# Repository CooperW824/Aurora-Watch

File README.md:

# Aurora-Watch
Project Aurora: The most over-engineered gimmick ever. A watch that is a compass, thermometer, step-counter, flashlight, all with a rechargable battery, and a processor 50x faster than the Apollo Guidance Computer.

## What is it?

It is a custom designed printed circuit board that contains a ring of 12 RGB LEDs, a microcontroller, and some senors to:
1. Display the current time. Where the red LED represents the hour hand, the green LED is the minute hand and the blue LED is the second hand.
2. Display the current ambient temperature using the number of LEDs lit and the color of the LEDs for the temperature.
3. A magnetic compass with the red LED pointing north, and the blue LED pointing south
4. A read out of the current battery charge using the LEDs
5. A built in step counter
5. A flashlight that uses the red LEDs to create a red-light flashlight
6. Rechargable LiPO battery using USB-C

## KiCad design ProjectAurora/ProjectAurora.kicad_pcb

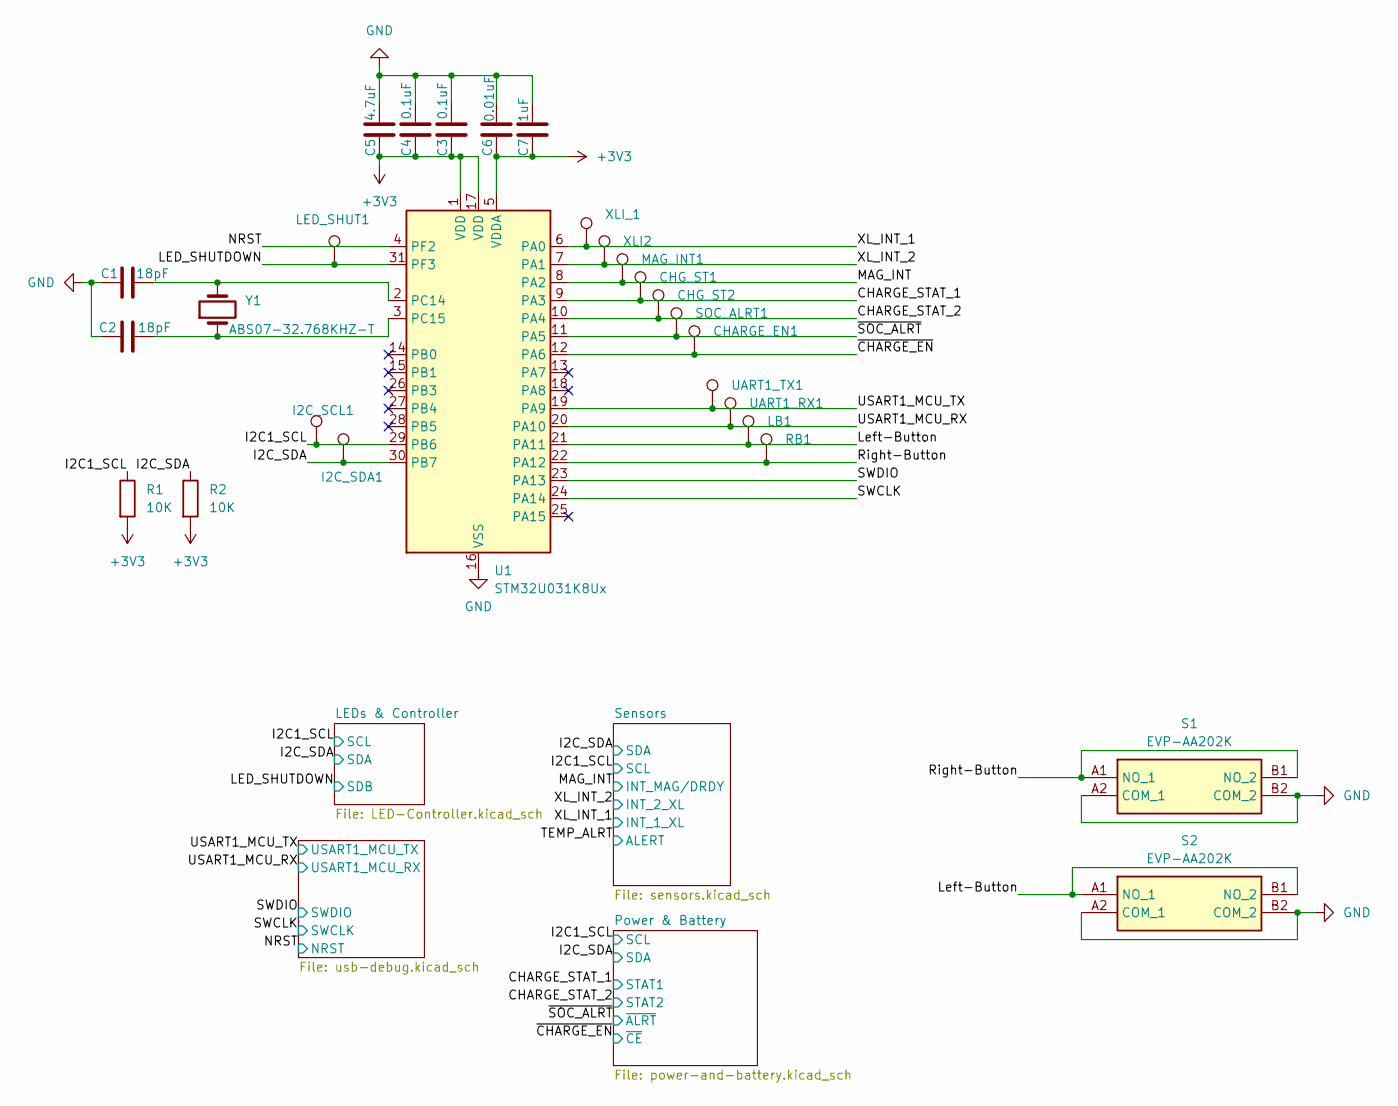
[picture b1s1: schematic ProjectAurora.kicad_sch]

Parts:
C1, C2: 18pF; C_0603_1608Metric
C3, C4: 0.1uF; C_0603_1608Metric
C5: 4.7uF; C_0603_1608Metric
C6: 0.01uF; C_0603_1608Metric
C7: 1uF; C_0603_1608Metric
CHARGE_EN1: TestPoint; TestPoint_Pad_1.0x1.0mm
CHG_ST1, CHG_ST2: TestPoint; TestPoint_Pad_1.0x1.0mm
I2C_SCL1, I2C_SDA1: TestPoint; TestPoint_Pad_1.0x1.0mm
LB1: TestPoint; TestPoint_Pad_1.0x1.0mm
LED_SHUT1: TestPoint; TestPoint_Pad_1.0x1.0mm
MAG_INT1: TestPoint; TestPoint_Pad_1.0x1.0mm
R1, R2: 10K; R_0603_1608Metric
RB1: TestPoint; TestPoint_Pad_1.0x1.0mm
S1, S2: EVP-AA202K; EVPAA202K; Mouser Part Number 667-EVP-AA202K
SOC_ALRT1: TestPoint; TestPoint_Pad_1.0x1.0mm
U1: STM32U031K8Ux; QFN-32-1EP_5x5mm_P0.5mm_EP3.45x3.45mm
UART1_RX1, UART1_TX1: TestPoint; TestPoint_Pad_1.0x1.0mm
XLI2: TestPoint; TestPoint_Pad_1.0x1.0mm
XLI_1: TestPoint; TestPoint_Pad_1.0x1.0mm
Y1: ABS07-32.768KHZ-T; ABS07

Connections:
/CHARGE_STAT_1: CHG_ST1.1, U1.9 (PA3); also elsewhere on the board
/CHARGE_STAT_2: CHG_ST2.1, U1.10 (PA4); also elsewhere on the board
/I2C1_SCL: I2C_SCL1.1, R1.1, U1.29 (PB6); also elsewhere on the board
/I2C_SDA: I2C_SDA1.1, R2.1, U1.30 (PB7); also elsewhere on the board
/LED_SHUTDOWN: LED_SHUT1.1, U1.31 (PF3); also elsewhere on the board
/Left-Button: LB1.1, S2.A1 (NO_1), S2.B1 (NO_2), U1.21 (PA11)
/MAG_INT: MAG_INT1.1, U1.8 (PA2); also elsewhere on the board
/NRST: U1.4 (PF2); also elsewhere on the board
/Right-Button: RB1.1, S1.A1 (NO_1), S1.B1 (NO_2), U1.22 (PA12)
/SWCLK: U1.24 (PA14); also elsewhere on the board
/SWDIO: U1.23 (PA13); also elsewhere on the board
/USART1_MCU_RX: U1.20 (PA10), UART1_RX1.1; also elsewhere on the board
/USART1_MCU_TX: U1.19 (PA9), UART1_TX1.1; also elsewhere on the board
/XL_INT_1: U1.6 (PA0), XLI_1.1; also elsewhere on the board
/XL_INT_2: U1.7 (PA1), XLI2.1; also elsewhere on the board
/~CHARGE_EN: CHARGE_EN1.1, U1.12 (PA6); also elsewhere on the board
/~SOC_ALRT: SOC_ALRT1.1, U1.11 (PA5); also elsewhere on the board
GND: C1.1, C2.1, C3.2, C4.2, C5.2, C6.2, C7.2, S1.A2 (COM_1), S1.B2 (COM_2), S2.A2 (COM_1), S2.B2 (COM_2), U1.16 (VSS), U1.32 (VSS), U1.33 (VSS); also elsewhere on the board
unnamed: C1.2, U1.2 (PC14), Y1.2
unnamed: C2.2, U1.3 (PC15), Y1.1

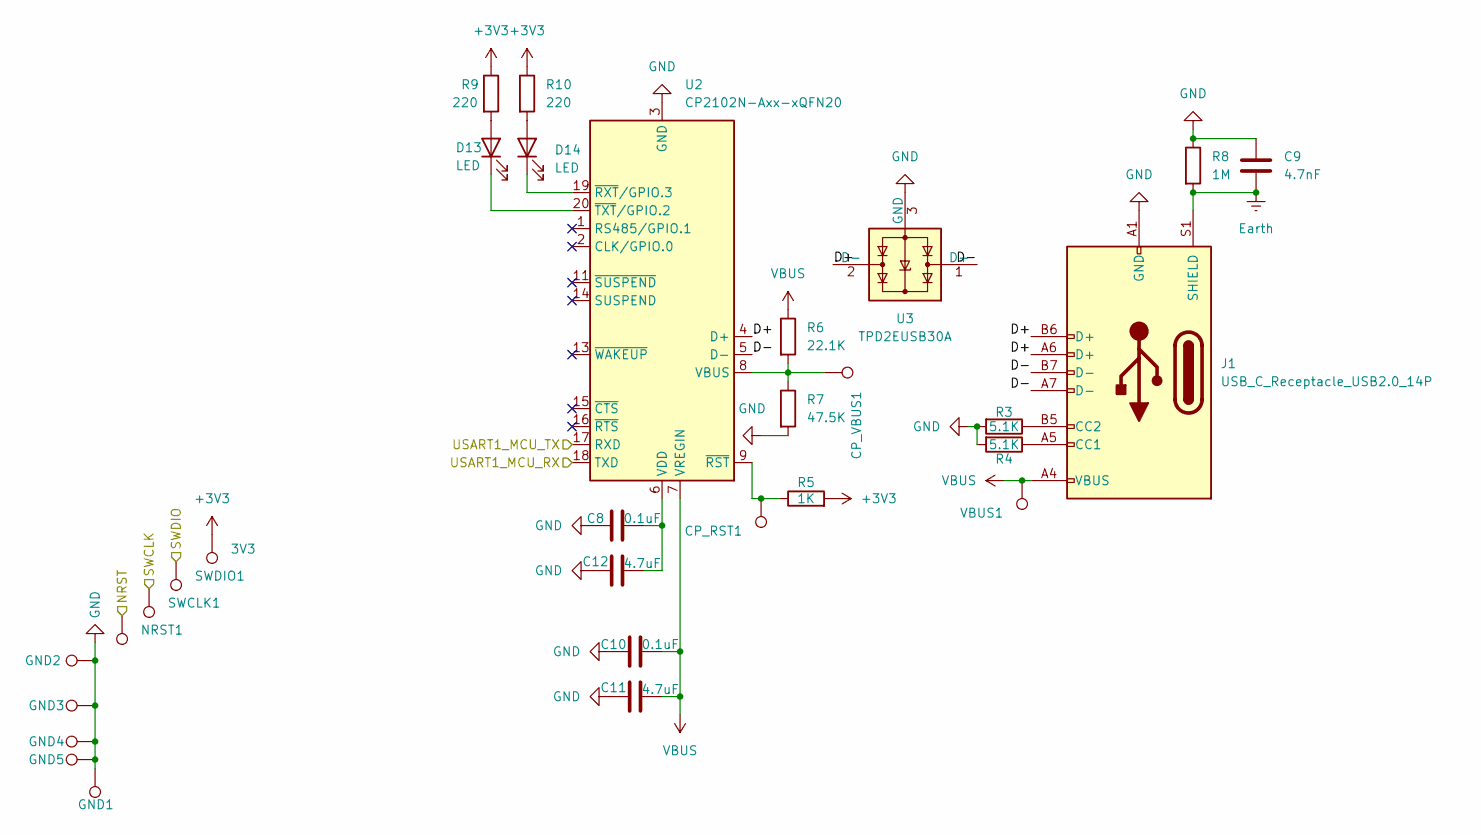
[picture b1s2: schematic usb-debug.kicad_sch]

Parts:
3V3: TestPoint; TestPoint_Pad_2.0x2.0mm
C8, C10: 0.1uF; C_0603_1608Metric
C9: 4.7nF; C_0603_1608Metric
C11, C12: 4.7uF; C_0603_1608Metric
CP_RST1: TestPoint; TestPoint_Pad_1.0x1.0mm
CP_VBUS1: TestPoint; TestPoint_Pad_1.0x1.0mm
D13, D14: LED; LED_0603_1608Metric
GND1: TestPoint; TestPoint_Pad_2.0x2.0mm
GND2, GND3, GND4, GND5: TestPoint; TestPoint_Pad_1.0x1.0mm
J1: USB_C_Receptacle_USB2.0_14P; USB_C_Receptacle_GCT_USB4105-xx-A_16P_TopMnt_Horizontal
NRST1: TestPoint; TestPoint_Pad_1.0x1.0mm
R3, R4: 5.1K; R_0603_1608Metric
R5: 1K; R_0603_1608Metric
R6: 22.1K; R_0603_1608Metric
R7: 47.5K; R_0603_1608Metric
R8: 1M; R_0603_1608Metric
R9, R10: 220; R_0603_1608Metric
SWCLK1: TestPoint; TestPoint_Pad_2.0x2.0mm
SWDIO1: TestPoint; TestPoint_Pad_2.0x2.0mm
U2: CP2102N-Axx-xQFN20; SiliconLabs_QFN-20-1EP_3x3mm_P0.5mm_EP1.8x1.8mm
U3: TPD2EUSB30A; Texas_DRT-3
VBUS1: TestPoint; TestPoint_Pad_1.0x1.0mm

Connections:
/NRST: NRST1.1; also elsewhere on the board
/SWCLK: SWCLK1.1; also elsewhere on the board
/SWDIO: SWDIO1.1; also elsewhere on the board
/USART1_MCU_RX: U2.18 (TXD); also elsewhere on the board
/USART1_MCU_TX: U2.17 (RXD); also elsewhere on the board
/USB & Debug/D+: J1.A6 (D+), J1.B6 (D+), U2.4 (D+), U3.2 (D-)
/USB & Debug/D-: J1.A7 (D-), J1.B7 (D-), U2.5 (D-), U3.1 (D+)
Earth: C9.2, J1.S1 (SHIELD), R8.2
GND: C8.1, C9.1, C10.1, C11.1, C12.1, GND1.1, GND2.1, GND3.1, GND4.1, GND5.1, J1.A1 (GND), J1.A12 (GND), J1.B1 (GND), J1.B12 (GND), R3.2, R4.2, R7.2, R8.1, U2.3 (GND), U2.12 (GND), U2.21 (GND), U3.3 (GND); also elsewhere on the board
unnamed: D13.2 (A), R9.2
unnamed: D13.1 (K), U2.20 (~TXT/GPIO.2)
unnamed: D14.2 (A), R10.2
unnamed: D14.1 (K), U2.19 (~RXT/GPIO.3)
unnamed: J1.A5 (CC1), R4.1
unnamed: J1.B5 (CC2), R3.1
unnamed: CP_VBUS1.1, R6.2, R7.1, U2.8 (VBUS)
unnamed: C8.2, C12.2, U2.6 (VDD)
unnamed: CP_RST1.1, R5.1, U2.9 (~RST)
VBUS: C10.2, C11.2, J1.A4 (VBUS), J1.A9 (VBUS), J1.B4 (VBUS), J1.B9 (VBUS), R6.1, U2.7 (VREGIN), VBUS1.1; also elsewhere on the board

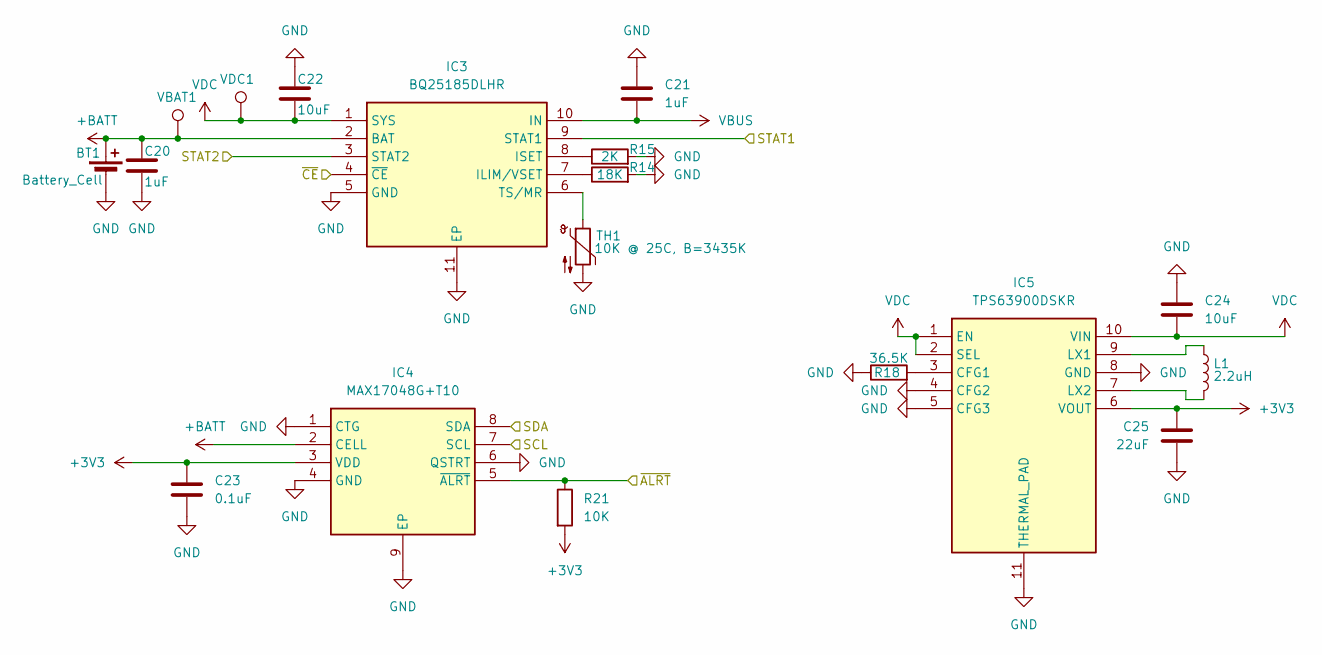
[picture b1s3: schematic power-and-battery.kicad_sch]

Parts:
BT1: Battery_Cell; JST_SH_SM02B-SRSS-TB_1x02-1MP_P1.00mm_Horizontal
C20, C21: 1uF; C_0603_1608Metric
C22, C24: 10uF; C_0603_1608Metric
C23: 0.1uF; C_0603_1608Metric
C25: 22uF; C_0603_1608Metric
IC3: BQ25185DLHR; Texas_DLH0010A_WSON-10-1EP_2.2x2mm_P0.4mm_EP0.9x1.5mm_Therm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; Mouser Part Number 595-BQ25185DLHR
IC4: MAX17048G+T10; TDFN-8-1EP_2x2mm_P0.5mm_EP0.8x1.2mm; Mouser Part Number 700-MAX17048G+T10
IC5: TPS63900DSKR; WSON-10-1EP_2.5x2.5mm_P0.5mm_EP1.2x2mm; Mouser Part Number 595-TPS63900DSKR
L1: 2.2uH; L_Coilcraft_0805HQ_2012Metric
R14: 18K; R_0603_1608Metric
R15: 2K; R_0603_1608Metric
R18: 36.5K; R_0603_1608Metric
R21: 10K; R_0603_1608Metric
TH1: 10K @ 25C, B=3435K; R_0603_1608Metric
VBAT1: TestPoint; TestPoint_Pad_1.0x1.0mm
VDC1: TestPoint; TestPoint_Pad_1.0x1.0mm

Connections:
+BATT: BT1.1 (+), C20.1, IC3.2 (BAT), IC4.2 (CELL), VBAT1.1
/CHARGE_STAT_1: IC3.9 (STAT1); also elsewhere on the board
/CHARGE_STAT_2: IC3.3 (STAT2); also elsewhere on the board
/I2C1_SCL: IC4.7 (SCL); also elsewhere on the board
/I2C_SDA: IC4.8 (SDA); also elsewhere on the board
/~CHARGE_EN: IC3.4 (~CE); also elsewhere on the board
/~SOC_ALRT: IC4.5 (~ALRT), R21.1; also elsewhere on the board
GND: BT1.2 (-), C20.2, C21.1, C22.1, C23.2, C24.1, C25.1, IC3.5 (GND), IC3.11 (EP), IC4.1 (CTG), IC4.4 (GND), IC4.6 (QSTRT), IC4.9 (EP), IC5.4 (CFG2), IC5.5 (CFG3), IC5.8 (GND), IC5.11 (THERMAL_PAD), R14.2, R15.2, R18.1, TH1.2; also elsewhere on the board
unnamed: IC3.7 (ILIM/VSET), R14.1
unnamed: IC3.8 (ISET), R15.1
unnamed: IC3.6 (TS/MR), TH1.1
unnamed: IC5.3 (CFG1), R18.2
unnamed: IC5.9 (LX1), L1.1
unnamed: IC5.7 (LX2), L1.2
VBUS: C21.2, IC3.10 (IN); also elsewhere on the board
VDC: C22.2, C24.2, IC3.1 (SYS), IC5.1 (EN), IC5.2 (SEL), IC5.10 (VIN), VDC1.1

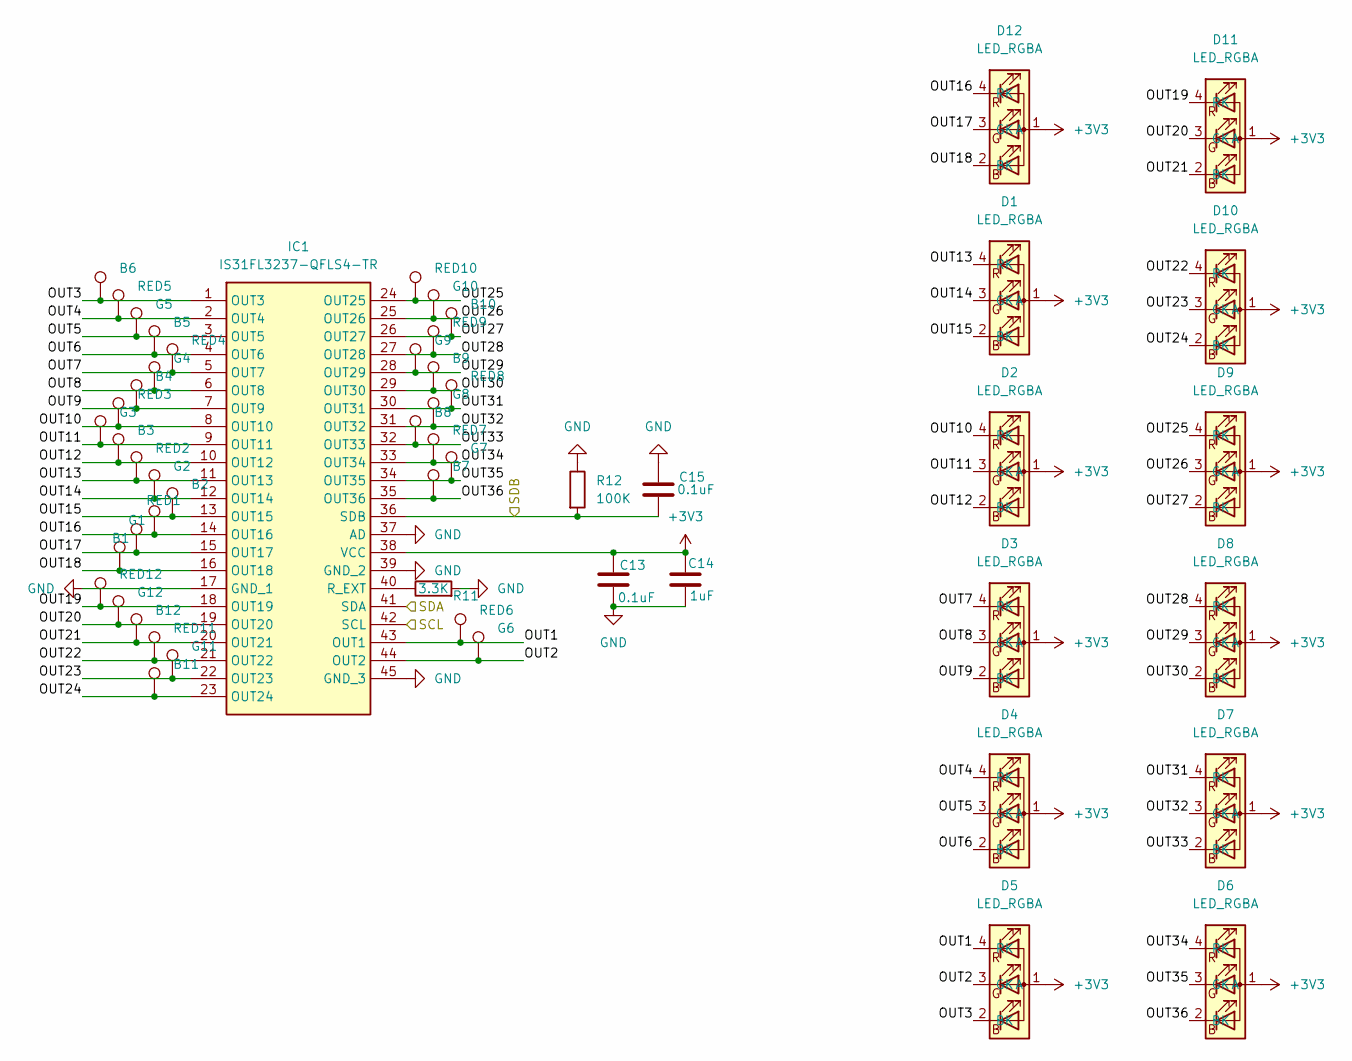
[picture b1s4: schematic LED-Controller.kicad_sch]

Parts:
B1, B2, B3, B4, B5, B6, B8, B9, B10, B11, B12: TestPoint; TestPoint_Pad_1.0x1.0mm
B7: `; TestPoint_Pad_1.0x1.0mm
C13, C15: 0.1uF; C_0603_1608Metric
C14: 1uF; C_0603_1608Metric
D1, D2, D3, D4, D5, D6, D7, D8, D9, D10, D11, D12: LED_RGBA; XL-1615RGBC-YG
G1, G2, G3, G4, G5, G6, G7, G8, G9, G10, G11, G12: TestPoint; TestPoint_Pad_1.0x1.0mm
IC1: IS31FL3237-QFLS4-TR; IS31FL3237QFLS4TR; Mouser Part Number 870-IS31FL3237QFLS4T
R11: 3.3K; R_0603_1608Metric
R12: 100K; R_0603_1608Metric
RED1, RED2, RED3, RED4, RED5, RED6, RED7, RED8, RED9, RED10, RED11, RED12: TestPoint; TestPoint_Pad_1.0x1.0mm

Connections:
/I2C1_SCL: IC1.42 (SCL); also elsewhere on the board
/I2C_SDA: IC1.41 (SDA); also elsewhere on the board
/LED_SHUTDOWN: C15.2, IC1.36 (SDB), R12.2; also elsewhere on the board
/LEDs & Controller/OUT1: D5.4 (RK), IC1.43 (OUT1), RED6.1
/LEDs & Controller/OUT2: D5.3 (GK), G6.1, IC1.44 (OUT2)
/LEDs & Controller/OUT3: B6.1, D5.2 (BK), IC1.1 (OUT3)
/LEDs & Controller/OUT4: D4.4 (RK), IC1.2 (OUT4), RED5.1
/LEDs & Controller/OUT5: D4.3 (GK), G5.1, IC1.3 (OUT5)
/LEDs & Controller/OUT6: B5.1, D4.2 (BK), IC1.4 (OUT6)
/LEDs & Controller/OUT7: D3.4 (RK), IC1.5 (OUT7), RED4.1
/LEDs & Controller/OUT8: D3.3 (GK), G4.1, IC1.6 (OUT8)
/LEDs & Controller/OUT9: B4.1, D3.2 (BK), IC1.7 (OUT9)
/LEDs & Controller/OUT10: D2.4 (RK), IC1.8 (OUT10), RED3.1
/LEDs & Controller/OUT11: D2.3 (GK), G3.1, IC1.9 (OUT11)
/LEDs & Controller/OUT12: B3.1, D2.2 (BK), IC1.10 (OUT12)
/LEDs & Controller/OUT13: D1.4 (RK), IC1.11 (OUT13), RED2.1
/LEDs & Controller/OUT14: D1.3 (GK), G2.1, IC1.12 (OUT14)
/LEDs & Controller/OUT15: B2.1, D1.2 (BK), IC1.13 (OUT15)
/LEDs & Controller/OUT16: D12.4 (RK), IC1.14 (OUT16), RED1.1
/LEDs & Controller/OUT17: D12.3 (GK), G1.1, IC1.15 (OUT17)
/LEDs & Controller/OUT18: B1.1, D12.2 (BK), IC1.16 (OUT18)
/LEDs & Controller/OUT19: D11.4 (RK), IC1.18 (OUT19), RED12.1
/LEDs & Controller/OUT20: D11.3 (GK), G12.1, IC1.19 (OUT20)
/LEDs & Controller/OUT21: B12.1, D11.2 (BK), IC1.20 (OUT21)
/LEDs & Controller/OUT22: D10.4 (RK), IC1.21 (OUT22), RED11.1
/LEDs & Controller/OUT23: D10.3 (GK), G11.1, IC1.22 (OUT23)
/LEDs & Controller/OUT24: B11.1, D10.2 (BK), IC1.23 (OUT24)
/LEDs & Controller/OUT25: D9.4 (RK), IC1.24 (OUT25), RED10.1
/LEDs & Controller/OUT26: D9.3 (GK), G10.1, IC1.25 (OUT26)
/LEDs & Controller/OUT27: B10.1, D9.2 (BK), IC1.26 (OUT27)
/LEDs & Controller/OUT28: D8.4 (RK), IC1.27 (OUT28), RED9.1
/LEDs & Controller/OUT29: D8.3 (GK), G9.1, IC1.28 (OUT29)
/LEDs & Controller/OUT30: B9.1, D8.2 (BK), IC1.29 (OUT30)
/LEDs & Controller/OUT31: D7.4 (RK), IC1.30 (OUT31), RED8.1
/LEDs & Controller/OUT32: D7.3 (GK), G8.1, IC1.31 (OUT32)
/LEDs & Controller/OUT33: B8.1, D7.2 (BK), IC1.32 (OUT33)
/LEDs & Controller/OUT34: D6.4 (RK), IC1.33 (OUT34), RED7.1
/LEDs & Controller/OUT35: D6.3 (GK), G7.1, IC1.34 (OUT35)
/LEDs & Controller/OUT36: B7.1, D6.2 (BK), IC1.35 (OUT36)
GND: C13.2, C14.2, C15.1, IC1.17 (GND_1), IC1.37 (AD), IC1.39 (GND_2), IC1.45 (GND_3), R11.2, R12.1; also elsewhere on the board
unnamed: IC1.40 (R_EXT), R11.1

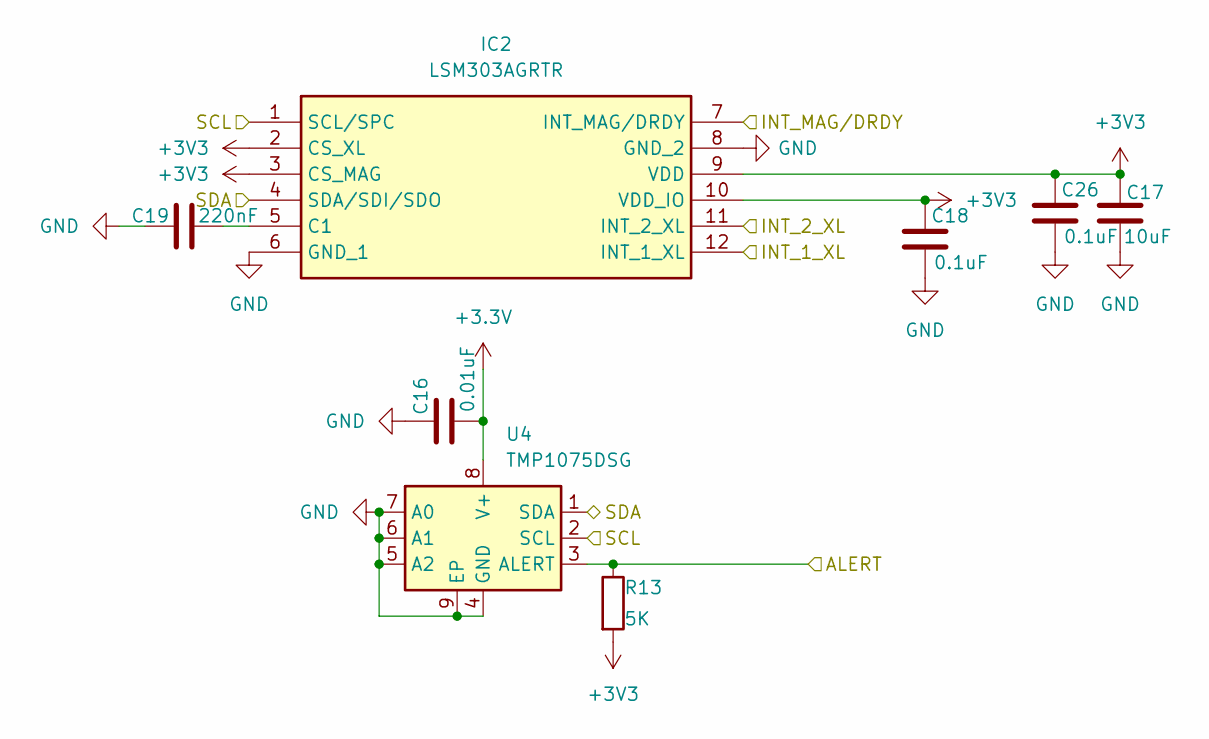
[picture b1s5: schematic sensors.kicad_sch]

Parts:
C16: 0.01uF; C_0603_1608Metric
C17: 10uF; C_0603_1608Metric
C18, C26: 0.1uF; C_0603_1608Metric
C19: 220nF; C_0603_1608Metric
IC2: LSM303AGRTR; LGA-12_2x2mm_P0.5mm; Mouser Part Number 511-LSM303AGRTR
R13: 5K; R_0603_1608Metric
U4: TMP1075DSG; WSON-8-1EP_2x2mm_P0.5mm_EP0.9x1.6mm_ThermalVias

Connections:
/I2C1_SCL: IC2.1 (SCL/SPC), U4.2 (SCL); also elsewhere on the board
/I2C_SDA: IC2.4 (SDA/SDI/SDO), U4.1 (SDA); also elsewhere on the board
/MAG_INT: IC2.7 (INT_MAG/DRDY); also elsewhere on the board
/XL_INT_1: IC2.12 (INT_1_XL); also elsewhere on the board
/XL_INT_2: IC2.11 (INT_2_XL); also elsewhere on the board
GND: C16.1, C17.2, C18.2, C19.2, C26.2, IC2.6 (GND_1), IC2.8 (GND_2), U4.4 (GND), U4.5 (A2), U4.6 (A1), U4.7 (A0), U4.9 (EP); also elsewhere on the board
unnamed: C19.1, IC2.5 (C1)
unnamed: R13.1, U4.3 (ALERT)

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
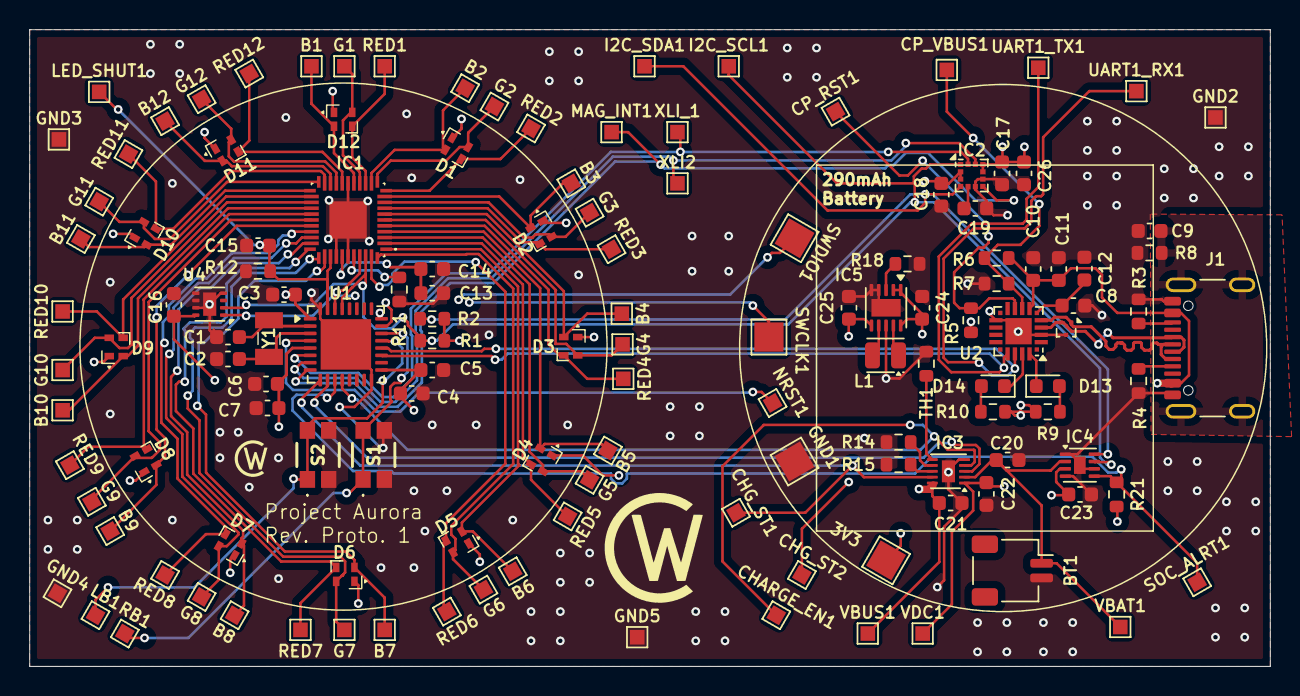
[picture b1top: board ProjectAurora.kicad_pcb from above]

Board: 4 copper layers, 84.8 x 43.5 mm, 136 parts (0 on the bottom side), 80 nets.

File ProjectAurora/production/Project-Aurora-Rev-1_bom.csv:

Designator,Footprint,Quantity,Value,LCSC Part #
"3V3, GND1, SWCLK1, SWDIO1",TestPoint_Pad_2.0x2.0mm,4,TestPoint,
"B1, B10, B11, B12, B2, B3, B4, B5, B6, B8, B9, CHARGE_EN1, CHG_ST1, CHG_ST2, CP_RST1, CP_VBUS1, G1, G10, G11, G12, G2, G3, G4, G5, G6, G7, G8, G9, GND2, GND3, GND4, GND5, I2C_SCL1, I2C_SDA1, LB1, LED_SHUT1, MAG_INT1, NRST1, RB1, RED1, RED10, RED11, RED12, RED2, RED3, RED4, RED5, RED6, RED7, RED8, RED9, SOC_ALRT1, UART1_RX1, UART1_TX1, VBAT1, VBUS1, VDC1, XLI2, XLI_1",TestPoint_Pad_1.0x1.0mm,59,TestPoint,
B7,TestPoint_Pad_1.0x1.0mm,1,`,
BT1,JST_SH_SM02B-SRSS-TB_1x02-1MP_P1.00mm_Horizontal,1,Battery_Cell,
"C1, C2",0603,2,18pF,
"C10, C13, C15, C18, C23, C26, C3, C4, C8",0603,9,0.1uF,
"C11, C12, C5",0603,3,4.7uF,
"C14, C20, C21, C7",0603,4,1uF,
"C16, C6",0603,2,0.01uF,
"C17, C22, C24",0603,3,10uF,
C19,0603,1,220nF,
C25,0603,1,22uF,
C9,0603,1,4.7nF,
"D1, D10, D11, D12, D2, D3, D4, D5, D6, D7, D8, D9",XL-1615RGBC-YG,12,LED_RGBA,
"D13, D14",0603,2,LED,
IC1,IS31FL3237QFLS4TR,1,IS31FL3237-QFLS4-TR,
IC2,LGA-12_2x2mm_P0.5mm,1,LSM303AGRTR,
IC3,Texas_DLH0010A_WSON-10-1EP_2.2x2mm_P0.4mm_EP0.9x1.5mm_ThermalVias,1,BQ25185DLHR,
IC4,TDFN-8-1EP_2x2mm_P0.5mm_EP0.8x1.2mm,1,MAX17048G+T10,
IC5,WSON-10-1EP_2.5x2.5mm_P0.5mm_EP1.2x2mm,1,TPS63900DSKR,
J1,USB_C_Receptacle_GCT_USB4105-xx-A_16P_TopMnt_Horizontal,1,USB_C_Receptacle_USB2.0_14P,
L1,L_Coilcraft_0805HQ_2012Metric,1,2.2uH,
"R1, R2, R21",0603,3,10K,
"R10, R9",0603,2,220,
R11,0603,1,3.3K,
R12,0603,1,100K,
R14,0603,1,18K,
R15,0603,1,2K,
R18,0603,1,36.5K,
"R3, R4",0603,2,5.1K,
R5,0603,1,1K,
R6,0603,1,22.1K,
R7,0603,1,47.5K,
R8,0603,1,1M,
"S1, S2",EVPAA202K,2,EVP-AA202K,
TH1,0603,1,"10K @ 25C, B=3435K",
U1,QFN-32-1EP_5x5mm_P0.5mm_EP3.45x3.45mm,1,STM32U031K8Ux,
U2,SiliconLabs_QFN-20-1EP_3x3mm_P0.5mm_EP1.8x1.8mm,1,CP2102N-Axx-xQFN20,
U3,Texas_DRT-3,1,TPD2EUSB30A,
U4,WSON-8-1EP_2x2mm_P0.5mm_EP0.9x1.6mm_ThermalVias,1,TMP1075DSG,
Y1,ABS07,1,ABS07-32.768KHZ-T,

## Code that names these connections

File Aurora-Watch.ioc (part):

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Mcu.Name=STM32U031K8Ux
Mcu.Package=UFQFPN32
Mcu.UserName=STM32U031K8Ux
PA0-CK_IN.GPIOParameters=GPIO_Label
PA0-CK_IN.GPIO_Label=XL_INT_1 (EXTI0)
PA0-CK_IN.Signal=GPXTI0
PA1.GPIOParameters=GPIO_Label
PA1.GPIO_Label=XL_INT_2 (EXTI1)
PA1.Signal=GPXTI1
PA10.Mode=Asynchronous
PA10.Signal=USART1_RX
PA11\ [PA9].GPIOParameters=GPIO_Label
PA11\ [PA9].GPIO_Label=LEFT_BUTTON
PA11\ [PA9].Signal=GPXTI11
PA12\ [PA10].GPIOParameters=GPIO_Label
PA12\ [PA10].GPIO_Label=RIGHT_BUTTON
PA12\ [PA10].Signal=GPXTI12
PA13\ (SWDIO).Mode=Serial_Wire
PA13\ (SWDIO).Signal=DEBUG_JTMS-SWDIO
PA14\ (SWCLK).Mode=Serial_Wire
PA14\ (SWCLK).Signal=DEBUG_JTCK-SWCLK
PA2.GPIOParameters=GPIO_Label
PA2.GPIO_Label=MAG_INT (EXTI2)
PA2.Signal=GPXTI2
PA3.GPIOParameters=GPIO_Label
PA3.GPIO_Label=CHARGE_STAT_1
PA3.Signal=GPXTI3
PA4.GPIOParameters=GPIO_Label
PA4.GPIO_Label=CHARGE_STAT_2
PA4.Signal=GPXTI4
PA5.GPIOParameters=GPIO_Label
PA5.GPIO_Label=SOC_ALRT
PA5.Signal=GPXTI5
PA6.GPIOParameters=GPIO_Label
PA6.GPIO_Label=CHARGE_EN
PA6.Signal=GPXTI6
PA9.Mode=Asynchronous
PA9.Signal=USART1_TX
PB6.Mode=I2C
PB6.Signal=I2C1_SCL
PB7.Mode=I2C
PB7.Signal=I2C1_SDA
PC14-OSC32_IN.Mode=LSE-External-Oscillator
PC14-OSC32_IN.Signal=RCC_OSC32_IN
PC15-OSC32_OUT.Mode=LSE-External-Oscillator
PC15-OSC32_OUT.Signal=RCC_OSC32_OUT
PF2-NRST.Signal=GPIO_Input
PF3-BOOT0\ (BOOT0).GPIOParameters=GPIO_Label
PF3-BOOT0\ (BOOT0).GPIO_Label=LED_SHUTDOWN
PF3-BOOT0\ (BOOT0).Signal=GPIO_Output
RCC.HSE_VALUE=4000000
RCC.SYSCLKFreq_VALUE=48000000
RCC.SYSCLKSource=RCC_SYSCLKSOURCE_PLLCLK
board=custom

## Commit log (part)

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2026-03-14 Component Selection and Refining Requirements
2026-03-25 First Schematics
2026-03-25 Remove the annoying files
2026-04-04 Sensors and LEDs
2026-04-05 Schematic Done
2026-05-13 Starting Layout
2026-05-19 Prototype Board Layout Done
2026-05-19 Prototype Board Ready for Ordering
2026-06-03 Setting Up the Firmware
2026-06-03 Blinky Is Not Yet Working
